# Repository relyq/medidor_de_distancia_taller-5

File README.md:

# medidor_de_distancia_taller-5

esquematica y diseño de pcb del proyecto del medidor de distancia de 5º año 2018<br>
./CAMOutputs/ - gerber medidor<br>
./CAMOutputs_display/ - gerber display<br>
./medidor/ - directorio del proyecto de eagle con los .sch y .brd<br>
./docs/ - directorio con las datasheets<br>

<h1>PDF</h1>
./medidor-botmirr.pdf - diseño de pcb lado inferior espejado<br>
./medidor-top.pdf - diseño de pcb lado superior<br>
./medidor-componentes.pdf - dibujo de componentes con diseño inferior y superior<br>
./medidorsch.pdf - esquematica<br>
<br>
./display.pdf - diseño de pcb de la placa para displays<br>
./display-componentes.pdf - componentes de placa de displays<br>

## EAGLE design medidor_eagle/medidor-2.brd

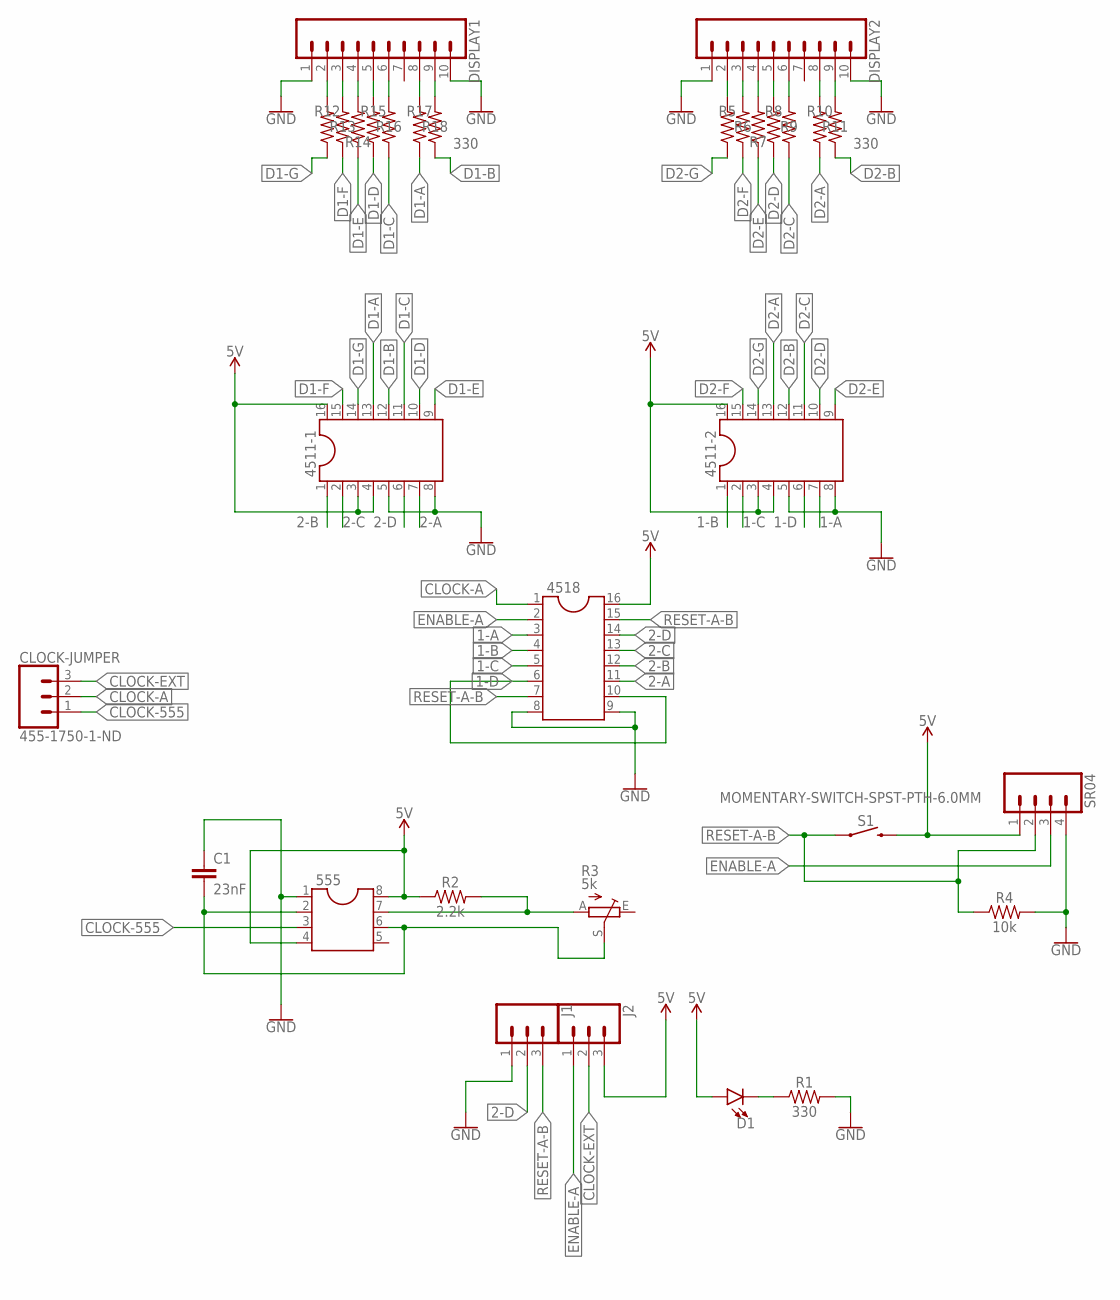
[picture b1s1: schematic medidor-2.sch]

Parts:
555: DIL8; DIL08
4511-1, 4511-2, 4518: DIL16
C1: 23nF; C2.5-3
CLOCK-JUMPER: 455-1750-1-ND; 1X03
D1: LED5MM; LED_5MM
DISPLAY1, DISPLAY2: CONN_10"; 1X10
J1, J2: CONN_03-SCREW-5MM; SCREWTERMINAL-5MM-3
R1, R5, R6, R7, R8, R9, R10, R11, R12, R13, R14, R15, R16, R17, R18: 330; AXIAL-0.3
R2: 2.2k; AXIAL-0.3
R3: 5k; B25P
R4: 10k; AXIAL-0.3
S1: MOMENTARY-SWITCH-SPST-PTH-6.0MM; TACTILE_SWITCH_PTH_6.0MM
SR04: CONN_04PTH; 1X04

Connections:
1-A: 4511-2.7, 4518.3
1-B: 4511-2.1, 4518.4
1-C: 4511-2.2, 4518.5
1-D: 4511-2.6, 4518.6, 4518.10
2-A: 4511-1.7, 4518.11
2-B: 4511-1.1, 4518.12
2-C: 4511-1.2, 4518.13
2-D: 4511-1.6, 4518.14, J1.2
5V: 555.4, 555.8, 4511-1.3, 4511-1.4, 4511-1.16, 4511-2.3, 4511-2.4, 4511-2.16, 4518.16, D1.A, J2.3, R2.P$1 (1), S1.3 (2), SR04.1
CLOCK-555: 555.3, CLOCK-JUMPER.1
CLOCK-A: 4518.1, CLOCK-JUMPER.2
CLOCK-EXT: CLOCK-JUMPER.3, J2.2
D1-A: 4511-1.13, R17.P$1 (1)
D1-B: 4511-1.12, R18.P$1 (1)
D1-C: 4511-1.11, R16.P$1 (1)
D1-D: 4511-1.10, R15.P$1 (1)
D1-E: 4511-1.9, R14.P$1 (1)
D1-F: 4511-1.15, R13.P$1 (1)
D1-G: 4511-1.14, R12.P$1 (1)
D2-A: 4511-2.13, R10.P$1 (1)
D2-B: 4511-2.12, R11.P$1 (1)
D2-C: 4511-2.11, R9.P$1 (1)
D2-D: 4511-2.10, R8.P$1 (1)
D2-E: 4511-2.9, R7.P$1 (1)
D2-F: 4511-2.15, R6.P$1 (1)
D2-G: 4511-2.14, R5.P$1 (1)
ENABLE-A: 4518.2, J2.1, SR04.3
GND: 555.1, 4511-1.5, 4511-1.8, 4511-2.5, 4511-2.8, 4518.8, 4518.9, C1.1, DISPLAY1.1, DISPLAY1.10, DISPLAY2.1, DISPLAY2.10, J1.1, R1.P$2 (2), R4.P$2 (2), SR04.4
unnamed: D1.K (C), R1.P$1 (1)
unnamed: DISPLAY1.2, R12.P$2 (2)
unnamed: 555.7, R2.P$2 (2), R3.A
unnamed: 555.2, 555.6, C1.2, R3.S
unnamed: DISPLAY1.3, R13.P$2 (2)
unnamed: DISPLAY1.4, R14.P$2 (2)
unnamed: DISPLAY1.5, R15.P$2 (2)
unnamed: DISPLAY1.6, R16.P$2 (2)
unnamed: DISPLAY1.8, R17.P$2 (2)
unnamed: DISPLAY1.9, R18.P$2 (2)
unnamed: DISPLAY2.2, R5.P$2 (2)
unnamed: DISPLAY2.3, R6.P$2 (2)
unnamed: DISPLAY2.4, R7.P$2 (2)
unnamed: DISPLAY2.5, R8.P$2 (2)
unnamed: DISPLAY2.6, R9.P$2 (2)
unnamed: DISPLAY2.8, R10.P$2 (2)
unnamed: DISPLAY2.9, R11.P$2 (2)
RESET-A-B: 4518.7, 4518.15, J1.3, R4.P$1 (1), S1.1, SR04.2

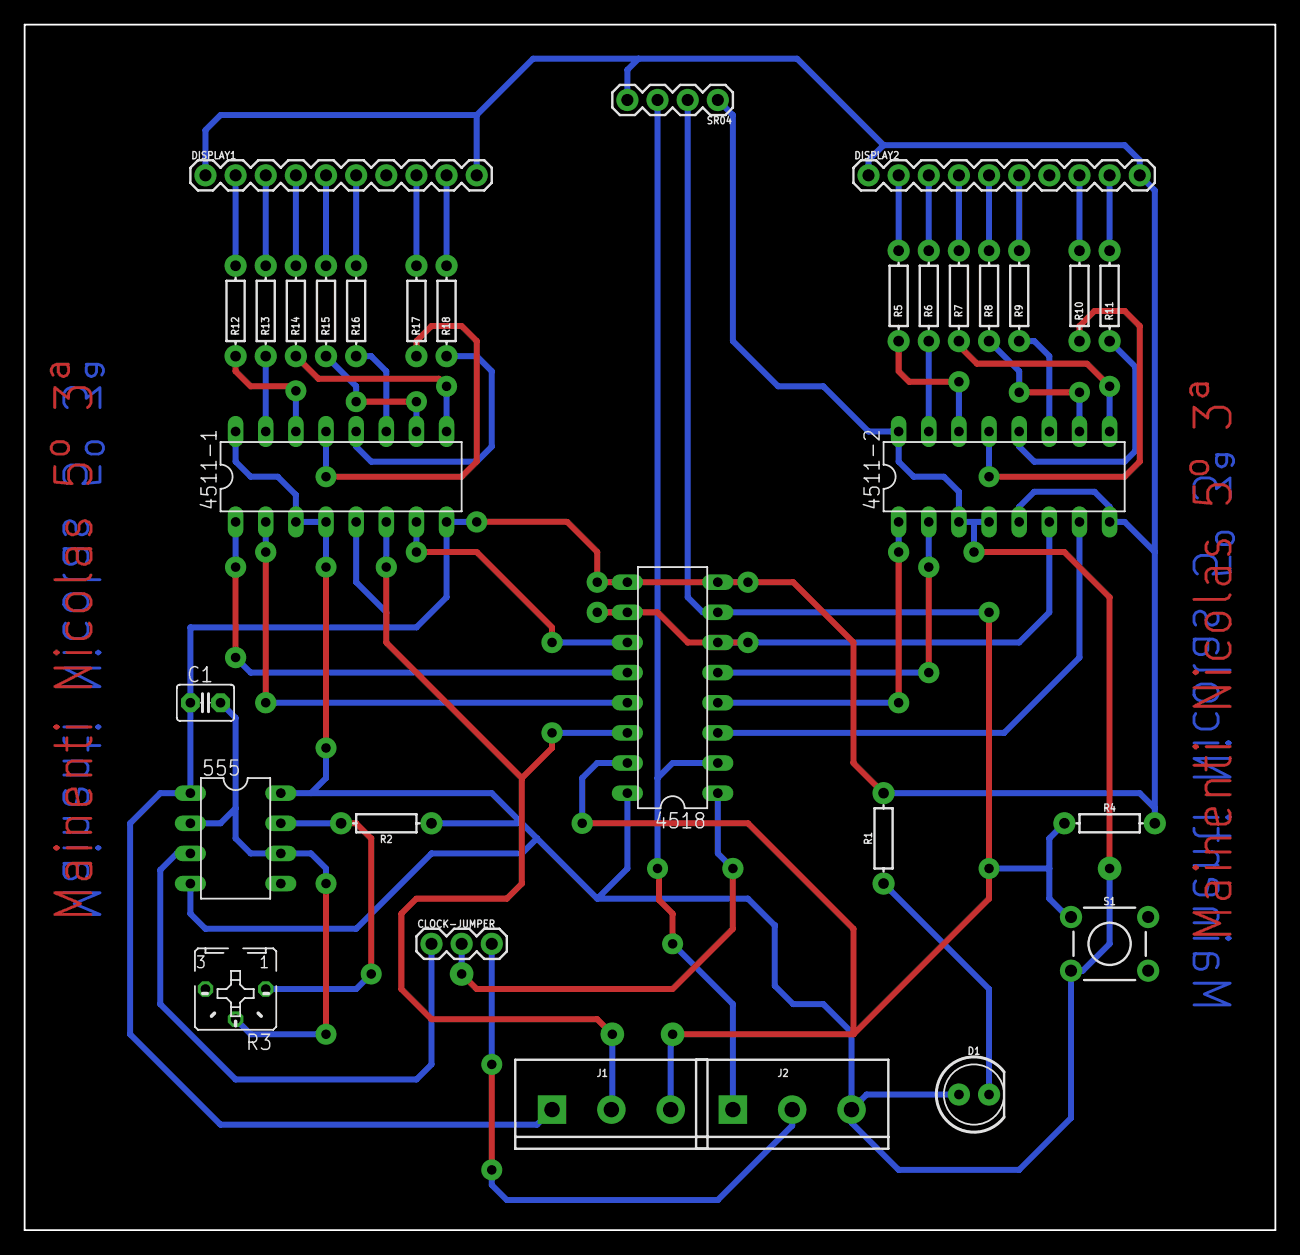
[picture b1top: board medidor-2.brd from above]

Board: 2 copper layers, 105.4 x 101.6 mm, 31 parts (0 on the bottom side), 46 nets.

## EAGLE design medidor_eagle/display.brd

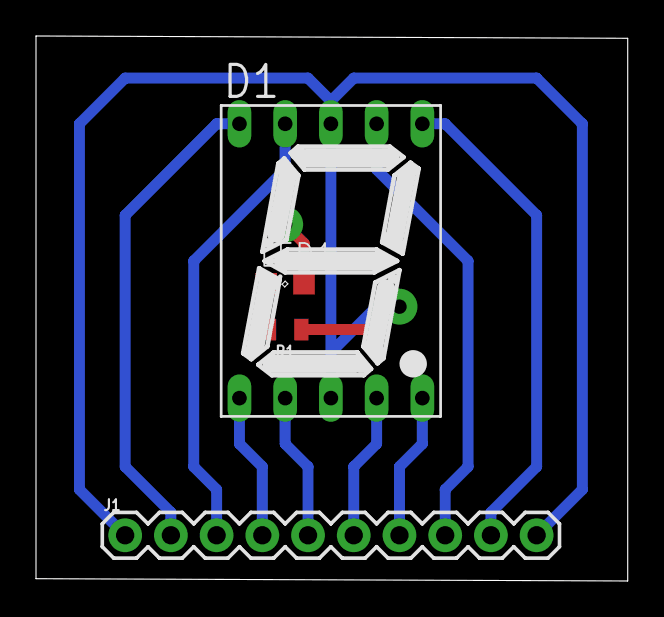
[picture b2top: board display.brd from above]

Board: 2 copper layers, 32.9 x 30.3 mm, 4 parts (0 on the bottom side), 10 nets.

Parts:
D1: 7SEG-13
J1: 1X10
LED1: SML0805
R1: 0805

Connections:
unnamed: D1.3, D1.8, J1.1, J1.10, R1.1
unnamed: LED1.C, R1.2
unnamed: D1.7, J1.8
unnamed: D1.6, J1.9
unnamed: D1.4, J1.6
unnamed: D1.2, J1.5
unnamed: D1.1, J1.4
unnamed: D1.9, J1.3, LED1.A
unnamed: D1.10, J1.2
unnamed: D1.5, J1.7

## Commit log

2020-08-24 gerber files
2020-08-27 esquematica
2021-02-14 aaaa
2021-02-19 ahora si funciona
2021-03-10 flatcam
2021-03-10 displayCAM
2021-03-10 display_flatcam
2021-07-13 eagle files
2021-09-04 archivos gerber
2021-09-04 soy mogolico
2021-10-27 informe de taller

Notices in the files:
parts and their libraries:
SparkFun-Connectors: Licensing: Creative Commons ShareAlike 4.0 International - https://creativecommons.org/licenses/by-sa/4.0
